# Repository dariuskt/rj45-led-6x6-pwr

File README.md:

---

6x6 ch led dimmer

Dev NOTE: before commit, run `./kibot.sh` to regenerate documentation, bom, gerbers and other assets.

* [schematics.pdf](gen/schematics.pdf)
* [pcb.pdf with dimensions](gen/pcb.pdf)

---

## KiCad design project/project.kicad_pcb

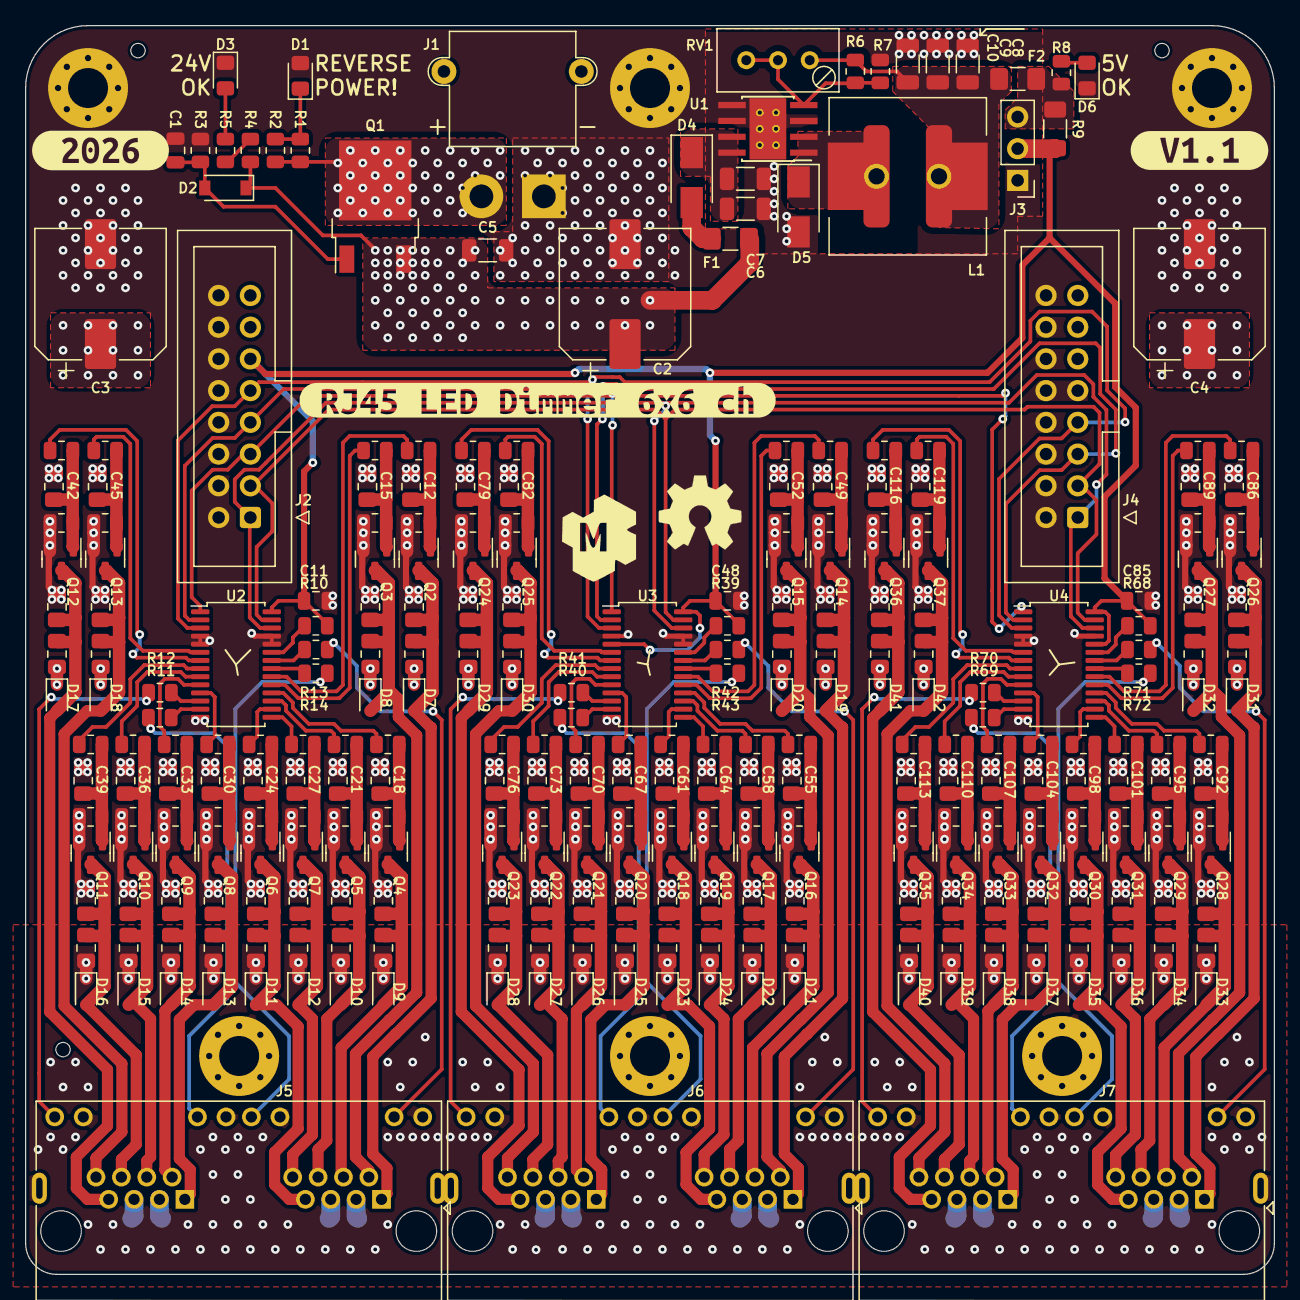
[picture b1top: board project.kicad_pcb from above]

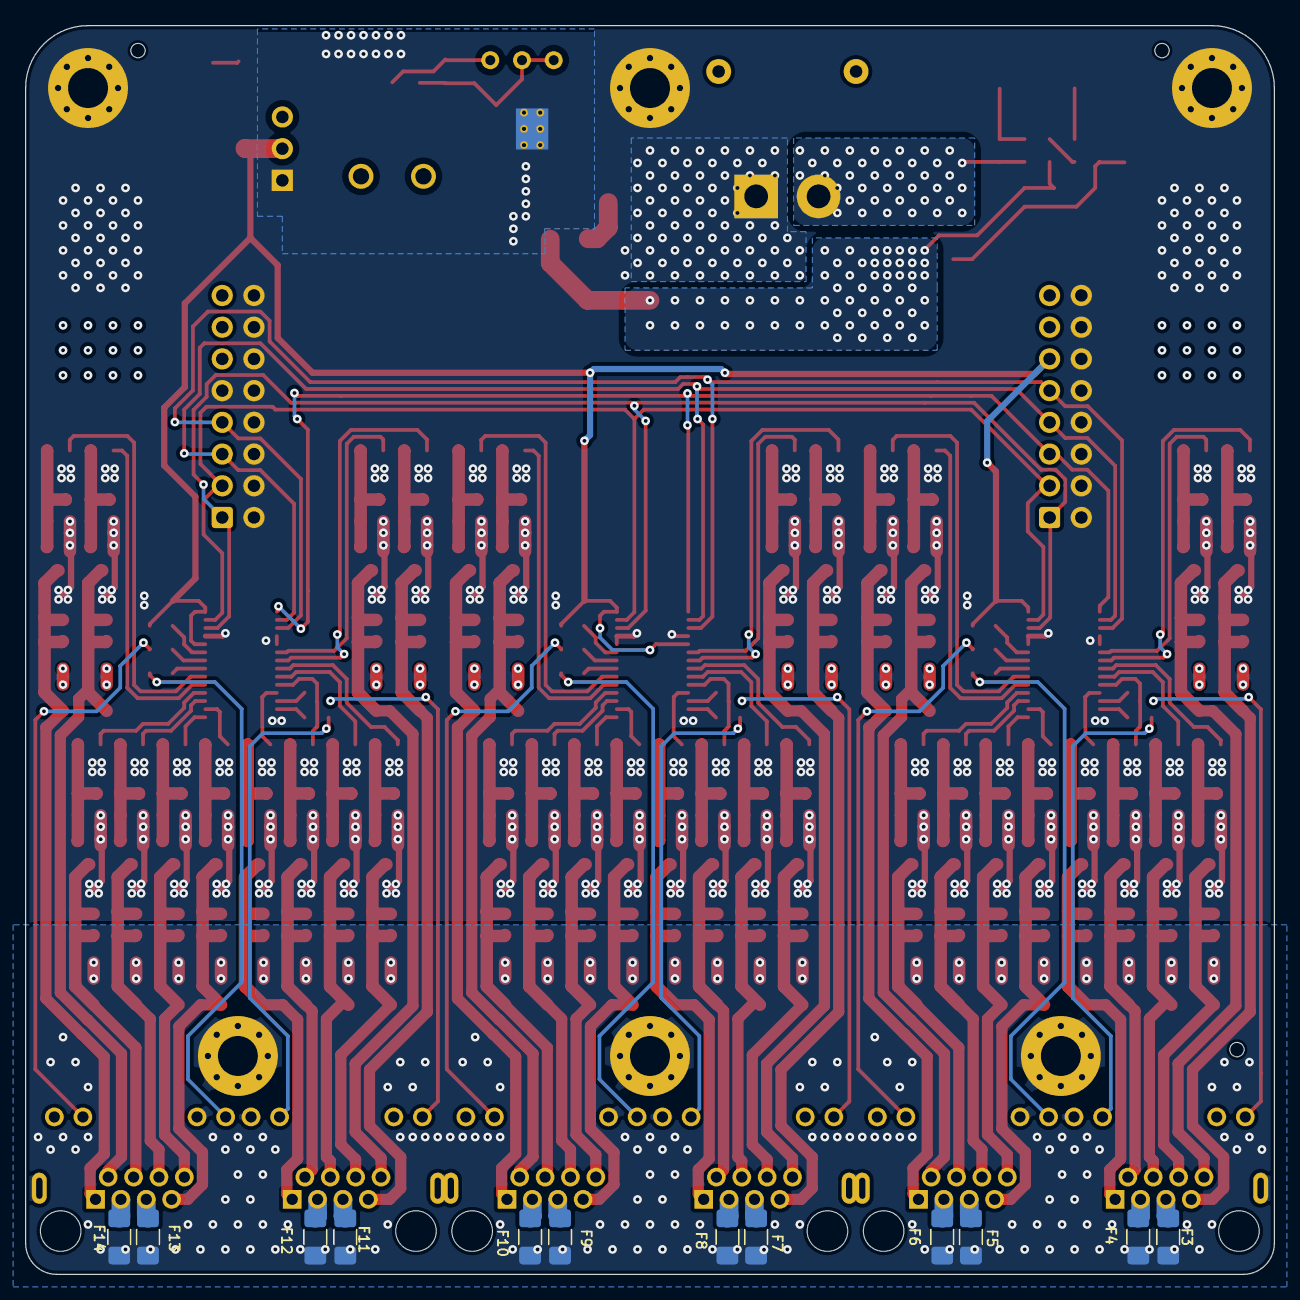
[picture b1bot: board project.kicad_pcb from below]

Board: 4 copper layers, 100.0 x 100.0 mm, 334 parts (12 on the bottom side), 167 nets.

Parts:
C1, C11, C48, C85: 100n; C_0805_2012Metric
C2, C3, C4: 220u/35v; CP_Elec_10x10
C5, C6, C7: 10u/35v; C_1206_3216Metric
C8, C9, C10: 100u/10v; C_1206_3216Metric
C12, C13, C14, C15, C16, C17, C18, C19, C20, C21, C22, C23, C24, C25, C26, C27, C28, C29, C30, C31, C32, C33, C34, C35, C36, C37, C38, C39, C40, C41, C42, C43, C44, C45, C46, C47, C49, C50, C51, C52, C53, C54, C55, C56, C57, C58, C59, C60, C61, C62, C63, C64, C65, C66, C67, C68, C69, C70, C71, C72, C73, C74, C75, C76, C77, C78, C79, C80, C81, C82, C83, C84, C86, C87, C88, C89, C90, C91, C92, C93, C94, C95, C96, C97, C98, C99, C100, C101, C102, C103, C104, C105, C106, C107, C108, C109, C110, C111, C112, C113, C114, C115, C116, C117, C118, C119, C120, C121: 10n; C_0805_2012Metric_Pad1.18x1.45mm_HandSolder
D1: LED-R; LED_0805_2012Metric_Pad1.15x1.40mm_HandSolder
D2: 11V; D_SOD-123
D3, D6: LED-G; LED_0805_2012Metric_Pad1.15x1.40mm_HandSolder
D4, D5: SS34; D_SMA
D7, D8, D9, D10, D11, D12, D13, D14, D15, D16, D17, D18, D19, D20, D21, D22, D23, D24, D25, D26, D27, D28, D29, D30, D31, D32, D33, D34, D35, D36, D37, D38, D39, D40, D41, D42: 1N5819WS; D_SOD-323
F1: 100mA; Fuse_1206_3216Metric_Pad1.42x1.75mm_HandSolder
F2: 300mA; Fuse_1206_3216Metric_Pad1.42x1.75mm_HandSolder
F3, F4, F5, F6, F7, F8, F9, F10, F11, F12, F13, F14: 1A; Fuse_1206_3216Metric_Pad1.42x1.75mm_HandSolder
G1: Logo_Open_Hardware_Large; OSHW-Symbol_6.7x6mm_SilkScreen
G2: LOGO_KMS; logo_kms_small_silkscreen
H1, H2, H3, H4, H5, H6: MP; MountingHole_3.2mm_M3_Pad_Via
J1: XT-IN; AMASS_XT30PW-M_1x02_P2.50mm_Horizontal
J2: IN; IDC-Header_2x08_P2.54mm_Vertical
J3: 5V; PinHeader_1x03_P2.54mm_Vertical
J4: OUT; IDC-Header_2x08_P2.54mm_Vertical
J5, J6, J7: RJ45_LED_Shielded_x2; RJ45_CONNFLY-Elec_DS1129-04-S8B0P-X
L1: 47u/2.5A; L_12x12mm_H8mm__D11.0_P5.0_universal
Q1: HYG210P06LQ1D; TO-252-2
Q2, Q3, Q4, Q5, Q6, Q7, Q8, Q9, Q10, Q11, Q12, Q13, Q14, Q15, Q16, Q17, Q18, Q19, Q20, Q21, Q22, Q23, Q24, Q25, Q26, Q27, Q28, Q29, Q30, Q31, Q32, Q33, Q34, Q35, Q36, Q37: AO3400A; SOT-23
R1, R2, R3, R4, R5, R10, R39, R68: 10k; R_0805_2012Metric
R6, R8, R11, R12, R13, R14, R40, R41, R42, R43, R69, R70, R71, R72: 4k7; R_0805_2012Metric
R7: 1k5; R_0805_2012Metric
R9: 0R1; R_1206_3216Metric_Pad1.30x1.75mm_HandSolder
R15, R17, R19, R21, R23, R25, R27, R29, R31, R33, R35, R37, R44, R46, R48, R50, R52, R54, R56, R58, R60, R62, R64, R66, R73, R75, R77, R79, R81, R83, R85, R87, R89, R91, R93, R95: 1K; R_0805_2012Metric
R16, R18, R20, R22, R24, R26, R28, R30, R32, R34, R36, R38, R45, R47, R49, R51, R53, R55, R57, R59, R61, R63, R65, R67, R74, R76, R78, R80, R82, R84, R86, R88, R90, R92, R94, R96: 100K; R_0805_2012Metric
RV1: 5k; Potentiometer_Bourns_3296W_Vertical
U1: XL4001; Texas_HTSOP-8-1EP_3.9x4.9mm_P1.27mm_EP2.95x4.9mm_Mask2.4x3.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
U2, U3, U4: PCA9685PW; TSSOP-28_4.4x9.7mm_P0.65mm
kibuzzard-69BFE35C: G***; kibuzzard-69BFE35C
kibuzzard-69BFE365: G***; kibuzzard-69BFE365
kibuzzard-67852857: G***; kibuzzard-67852857

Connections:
+5V: C11.1, C48.1, C85.1, J2.11, J3.2, R9.2, R10.1, R39.1, R68.1, U2.28 (VDD), U3.5 (A4), U3.28 (VDD), U4.24 (A5), U4.28 (VDD)
+24V: C2.1, C3.1, C4.1, C5.1, C13.1, C16.1, C19.1, C22.1, C25.1, C28.1, C31.1, C34.1, C37.1, C40.1, C43.1, C46.1, C50.1, C53.1, C56.1, C59.1, C62.1, C65.1, C68.1, C71.1, C74.1, C77.1, C80.1, C83.1, C87.1, C90.1, C93.1, C96.1, C99.1, C102.1, C105.1, C108.1, C111.1, C114.1, C117.1, C120.1, D2.1 (K), D7.1 (K), D8.1 (K), D9.1 (K), D10.1 (K), D11.1 (K), D12.1 (K), D13.1 (K), D14.1 (K), D15.1 (K), D16.1 (K), D17.1 (K), D18.1 (K), D19.1 (K), D20.1 (K), D21.1 (K), D22.1 (K), D23.1 (K), D24.1 (K), D25.1 (K), D26.1 (K), D27.1 (K), D28.1 (K), D29.1 (K), D30.1 (K), D31.1 (K), D32.1 (K), D33.1 (K), D34.1 (K), D35.1 (K), D36.1 (K), D37.1 (K), D38.1 (K), D39.1 (K), D40.1 (K), D41.1 (K), D42.1 (K), F1.1, F3.1, F4.1, F5.1, F6.1, F7.1, F8.1, F9.1, F10.1, F11.1, F12.1, F13.1, F14.1, Q1.3 (S), R4.2
/FB: R6.2, R7.1, RV1.2, RV1.3, U1.4 (FB)
/SW: D5.1 (K), L1.1, U1.1 (SW), U1.2 (SW)
/VIN: J1.2, Q1.2 (D), R1.1, R2.1
/VINp: C6.1, C7.1, D4.1 (K), U1.7 (VIN), U1.8 (VIN)
/VOUTf: F2.2, J3.3, R8.2, R9.1
/VOUTp: C8.1, C9.1, C10.1, F2.1, L1.2, R6.1, RV1.1
/_double_port_pwr1/1Blue: C22.2, C23.1, D10.2 (A), J5.6, Q5.3 (D)
/_double_port_pwr1/1Green: C19.2, C20.1, D9.2 (A), J5.4, Q4.3 (D)
/_double_port_pwr1/1Red: C16.2, C17.1, D8.2 (A), J5.2, Q3.3 (D)
/_double_port_pwr1/1TBD: C25.2, C26.1, D11.2 (A), J5.7, Q6.3 (D)
/_double_port_pwr1/1White2: C28.2, C29.1, D12.2 (A), J5.8, Q7.3 (D)
/_double_port_pwr1/1white1: C13.2, C14.1, D7.2 (A), J5.1, Q2.3 (D)
/_double_port_pwr1/2Blue: C40.2, C41.1, D16.2 (A), J5.18, Q11.3 (D)
/_double_port_pwr1/2Green: C37.2, C38.1, D15.2 (A), J5.16, Q10.3 (D)
/_double_port_pwr1/2Red: C34.2, C35.1, D14.2 (A), J5.14, Q9.3 (D)
/_double_port_pwr1/2TBD: C43.2, C44.1, D17.2 (A), J5.19, Q12.3 (D)
/_double_port_pwr1/2White2: C46.2, C47.1, D18.2 (A), J5.20, Q13.3 (D)
/_double_port_pwr1/2white1: C31.2, C32.1, D13.2 (A), J5.13, Q8.3 (D)
/_double_port_pwr1/LED11: R12.2, U2.12 (LED6)
/_double_port_pwr1/LED12: R11.2, U2.13 (LED7)
/_double_port_pwr1/LED21: R14.2, U2.21 (LED14)
/_double_port_pwr1/LED22: R13.2, U2.22 (LED15)
/_double_port_pwr1/_single_channel_pwr_13/IN: R35.1, U2.7 (LED1)
/_double_port_pwr1/_single_channel_pwr_14/IN: R33.1, U2.8 (LED2)
/_double_port_pwr1/_single_channel_pwr_15/IN: R37.1, U2.6 (LED0)
/_double_port_pwr1/_single_channel_pwr_16/IN: R15.1, U2.20 (LED13)
/_double_port_pwr1/_single_channel_pwr_17/IN: R17.1, U2.19 (LED12)
/_double_port_pwr1/_single_channel_pwr_18/IN: R23.1, U2.16 (LED9)
/_double_port_pwr1/_single_channel_pwr_19/IN: R27.1, U2.11 (LED5)
/_double_port_pwr1/_single_channel_pwr_20/IN: R19.1, U2.18 (LED11)
/_double_port_pwr1/_single_channel_pwr_21/IN: R21.1, U2.17 (LED10)
/_double_port_pwr1/_single_channel_pwr_22/IN: R25.1, U2.15 (LED8)
/_double_port_pwr1/_single_channel_pwr_23/IN: R29.1, U2.10 (LED4)
/_double_port_pwr1/_single_channel_pwr_24/IN: R31.1, U2.9 (LED3)
/_double_port_pwr1//OE: R10.2, U2.23 (~OE)
/_double_port_pwr2/1Blue: C59.2, C60.1, D22.2 (A), J6.6, Q17.3 (D)
/_double_port_pwr2/1Green: C56.2, C57.1, D21.2 (A), J6.4, Q16.3 (D)
/_double_port_pwr2/1Red: C53.2, C54.1, D20.2 (A), J6.2, Q15.3 (D)
/_double_port_pwr2/1TBD: C62.2, C63.1, D23.2 (A), J6.7, Q18.3 (D)
/_double_port_pwr2/1White2: C65.2, C66.1, D24.2 (A), J6.8, Q19.3 (D)
/_double_port_pwr2/1white1: C50.2, C51.1, D19.2 (A), J6.1, Q14.3 (D)
/_double_port_pwr2/2Blue: C77.2, C78.1, D28.2 (A), J6.18, Q23.3 (D)
/_double_port_pwr2/2Green: C74.2, C75.1, D27.2 (A), J6.16, Q22.3 (D)
/_double_port_pwr2/2Red: C71.2, C72.1, D26.2 (A), J6.14, Q21.3 (D)
/_double_port_pwr2/2TBD: C80.2, C81.1, D29.2 (A), J6.19, Q24.3 (D)
/_double_port_pwr2/2White2: C83.2, C84.1, D30.2 (A), J6.20, Q25.3 (D)
/_double_port_pwr2/2white1: C68.2, C69.1, D25.2 (A), J6.13, Q20.3 (D)
/_double_port_pwr2/LED11: R41.2, U3.12 (LED6)
/_double_port_pwr2/LED12: R40.2, U3.13 (LED7)
/_double_port_pwr2/LED21: R43.2, U3.21 (LED14)
/_double_port_pwr2/LED22: R42.2, U3.22 (LED15)
/_double_port_pwr2/_single_channel_pwr_13/IN: R64.1, U3.7 (LED1)
/_double_port_pwr2/_single_channel_pwr_14/IN: R62.1, U3.8 (LED2)
/_double_port_pwr2/_single_channel_pwr_15/IN: R66.1, U3.6 (LED0)
/_double_port_pwr2/_single_channel_pwr_16/IN: R44.1, U3.20 (LED13)
/_double_port_pwr2/_single_channel_pwr_17/IN: R46.1, U3.19 (LED12)
/_double_port_pwr2/_single_channel_pwr_18/IN: R52.1, U3.16 (LED9)
/_double_port_pwr2/_single_channel_pwr_19/IN: R56.1, U3.11 (LED5)
/_double_port_pwr2/_single_channel_pwr_20/IN: R48.1, U3.18 (LED11)
/_double_port_pwr2/_single_channel_pwr_21/IN: R50.1, U3.17 (LED10)
/_double_port_pwr2/_single_channel_pwr_22/IN: R54.1, U3.15 (LED8)
/_double_port_pwr2/_single_channel_pwr_23/IN: R58.1, U3.10 (LED4)
/_double_port_pwr2/_single_channel_pwr_24/IN: R60.1, U3.9 (LED3)
/_double_port_pwr2//OE: R39.2, U3.23 (~OE)
/_double_port_pwr3/1Blue: C96.2, C97.1, D34.2 (A), J7.6, Q29.3 (D)
/_double_port_pwr3/1Green: C93.2, C94.1, D33.2 (A), J7.4, Q28.3 (D)
/_double_port_pwr3/1Red: C90.2, C91.1, D32.2 (A), J7.2, Q27.3 (D)
/_double_port_pwr3/1TBD: C99.2, C100.1, D35.2 (A), J7.7, Q30.3 (D)
/_double_port_pwr3/1White2: C102.2, C103.1, D36.2 (A), J7.8, Q31.3 (D)
/_double_port_pwr3/1white1: C87.2, C88.1, D31.2 (A), J7.1, Q26.3 (D)
/_double_port_pwr3/2Blue: C114.2, C115.1, D40.2 (A), J7.18, Q35.3 (D)
/_double_port_pwr3/2Green: C111.2, C112.1, D39.2 (A), J7.16, Q34.3 (D)
/_double_port_pwr3/2Red: C108.2, C109.1, D38.2 (A), J7.14, Q33.3 (D)
/_double_port_pwr3/2TBD: C117.2, C118.1, D41.2 (A), J7.19, Q36.3 (D)
/_double_port_pwr3/2White2: C120.2, C121.1, D42.2 (A), J7.20, Q37.3 (D)
/_double_port_pwr3/2white1: C105.2, C106.1, D37.2 (A), J7.13, Q32.3 (D)
/_double_port_pwr3/LED11: R70.2, U4.12 (LED6)
/_double_port_pwr3/LED12: R69.2, U4.13 (LED7)
/_double_port_pwr3/LED21: R72.2, U4.21 (LED14)
/_double_port_pwr3/LED22: R71.2, U4.22 (LED15)
/_double_port_pwr3/_single_channel_pwr_13/IN: R93.1, U4.7 (LED1)
/_double_port_pwr3/_single_channel_pwr_14/IN: R91.1, U4.8 (LED2)
/_double_port_pwr3/_single_channel_pwr_15/IN: R95.1, U4.6 (LED0)
/_double_port_pwr3/_single_channel_pwr_16/IN: R73.1, U4.20 (LED13)
/_double_port_pwr3/_single_channel_pwr_17/IN: R75.1, U4.19 (LED12)
/_double_port_pwr3/_single_channel_pwr_18/IN: R81.1, U4.16 (LED9)
/_double_port_pwr3/_single_channel_pwr_19/IN: R85.1, U4.11 (LED5)
/_double_port_pwr3/_single_channel_pwr_20/IN: R77.1, U4.18 (LED11)
/_double_port_pwr3/_single_channel_pwr_21/IN: R79.1, U4.17 (LED10)
/_double_port_pwr3/_single_channel_pwr_22/IN: R83.1, U4.15 (LED8)
/_double_port_pwr3/_single_channel_pwr_23/IN: R87.1, U4.10 (LED4)
/_double_port_pwr3/_single_channel_pwr_24/IN: R89.1, U4.9 (LED3)
/_double_port_pwr3//OE: R68.2, U4.23 (~OE)
A0: J2.5, U2.1 (A0), U3.1 (A0), U4.1 (A0)
A1: J2.7, J4.5, U2.2 (A1), U3.2 (A1), U4.2 (A1)
A2: J2.9, J4.7, U2.3 (A2), U3.3 (A2), U4.3 (A2)
GND: C1.2, C2.2, C3.2, C4.2, C5.2, C6.2, C7.2, C8.2, C9.2, C10.2, C11.2, C12.2, C14.2, C15.2, C17.2, C18.2, C20.2, C21.2, C23.2, C24.2, C26.2, C27.2, C29.2, C30.2, C32.2, C33.2, C35.2, C36.2, C38.2, C39.2, C41.2, C42.2, C44.2, C45.2, C47.2, C48.2, C49.2, C51.2, C52.2, C54.2, C55.2, C57.2, C58.2, C60.2, C61.2, C63.2, C64.2, C66.2, C67.2, C69.2, C70.2, C72.2, C73.2, C75.2, C76.2, C78.2, C79.2, C81.2, C82.2, C84.2, C85.2, C86.2, C88.2, C89.2, C91.2, C92.2, C94.2, C95.2, C97.2, C98.2, C100.2, C101.2, C103.2, C104.2, C106.2, C107.2, C109.2, C110.2, C112.2, C113.2, C115.2, C116.2, C118.2, C119.2, C121.2, D1.2 (A), D3.1 (K), D5.2 (A), D6.1 (K), H1.1, H2.1, H3.1, H4.1, H5.1, H6.1, J1.1, J2.2, J2.4, J2.6, J2.8, J2.10, J2.12, J2.14, J2.16, J3.1, J4.2, J4.4, J4.6, J4.8, J4.9, J4.10, J4.12, J4.14, J4.16, J5.9, J5.11, J5.21, J5.23, J5.SH, J6.9, J6.11, J6.21, J6.23, J6.SH, J7.9, J7.11, J7.21, J7.23, J7.SH, Q2.2 (S), Q3.2 (S), Q4.2 (S), Q5.2 (S), Q6.2 (S), Q7.2 (S), Q8.2 (S), Q9.2 (S), Q10.2 (S), Q11.2 (S), Q12.2 (S), Q13.2 (S), Q14.2 (S), Q15.2 (S), Q16.2 (S), Q17.2 (S), Q18.2 (S), Q19.2 (S), Q20.2 (S), Q21.2 (S), Q22.2 (S), Q23.2 (S), Q24.2 (S), Q25.2 (S), Q26.2 (S), Q27.2 (S), Q28.2 (S), Q29.2 (S), Q30.2 (S), Q31.2 (S), Q32.2 (S), Q33.2 (S), Q34.2 (S), Q35.2 (S), Q36.2 (S), Q37.2 (S), R3.1, R7.2, R16.1, R18.1, R20.1, R22.1, R24.1, R26.1, R28.1, R30.1, R32.1, R34.1, R36.1, R38.1, R45.1, R47.1, R49.1, R51.1, R53.1, R55.1, R57.1, R59.1, R61.1, R63.1, R65.1, R67.1, R74.1, R76.1, R78.1, R80.1, R82.1, R84.1, R86.1, R88.1, R90.1, R92.1, R94.1, R96.1, U1.3 (GND), U1.5 (CS), U1.6 (EN), U1.9 (GND), U2.4 (A3), U2.5 (A4), U2.14 (VSS), U2.24 (A5), U2.25 (EXTCLK), U3.4 (A3), U3.14 (VSS), U3.24 (A5), U3.25 (EXTCLK), U4.4 (A3), U4.5 (A4), U4.14 (VSS), U4.25 (EXTCLK)
unnamed: C1.1, D2.2 (A), Q1.1 (G), R3.2
unnamed: C12.1, Q2.1 (G), R15.2, R16.2
unnamed: C15.1, Q3.1 (G), R17.2, R18.2
unnamed: C18.1, Q4.1 (G), R19.2, R20.2
unnamed: C21.1, Q5.1 (G), R21.2, R22.2
unnamed: C24.1, Q6.1 (G), R23.2, R24.2
unnamed: C27.1, Q7.1 (G), R25.2, R26.2
unnamed: C30.1, Q8.1 (G), R27.2, R28.2
unnamed: C33.1, Q9.1 (G), R29.2, R30.2
unnamed: C36.1, Q10.1 (G), R31.2, R32.2
unnamed: C39.1, Q11.1 (G), R33.2, R34.2
unnamed: C42.1, Q12.1 (G), R35.2, R36.2
unnamed: C45.1, Q13.1 (G), R37.2, R38.2
unnamed: C49.1, Q14.1 (G), R44.2, R45.2
unnamed: C52.1, Q15.1 (G), R46.2, R47.2
unnamed: C55.1, Q16.1 (G), R48.2, R49.2
unnamed: C58.1, Q17.1 (G), R50.2, R51.2
unnamed: C61.1, Q18.1 (G), R52.2, R53.2
unnamed: C64.1, Q19.1 (G), R54.2, R55.2
unnamed: C67.1, Q20.1 (G), R56.2, R57.2
unnamed: C70.1, Q21.1 (G), R58.2, R59.2
unnamed: C73.1, Q22.1 (G), R60.2, R61.2
unnamed: C76.1, Q23.1 (G), R62.2, R63.2
unnamed: C79.1, Q24.1 (G), R64.2, R65.2
unnamed: C82.1, Q25.1 (G), R66.2, R67.2
unnamed: C86.1, Q26.1 (G), R73.2, R74.2
unnamed: C89.1, Q27.1 (G), R75.2, R76.2
unnamed: C92.1, Q28.1 (G), R77.2, R78.2
unnamed: C95.1, Q29.1 (G), R79.2, R80.2
unnamed: C98.1, Q30.1 (G), R81.2, R82.2
unnamed: C101.1, Q31.1 (G), R83.2, R84.2
unnamed: C104.1, Q32.1 (G), R85.2, R86.2
unnamed: C107.1, Q33.1 (G), R87.2, R88.2
unnamed: C110.1, Q34.1 (G), R89.2, R90.2
unnamed: C113.1, Q35.1 (G), R91.2, R92.2
unnamed: C116.1, Q36.1 (G), R93.2, R94.2
unnamed: C119.1, Q37.1 (G), R95.2, R96.2
unnamed: D1.1 (K), R1.2, R2.2
unnamed: D3.2 (A), R5.1
unnamed: D4.2 (A), F1.2
unnamed: D6.2 (A), R8.1
unnamed: F3.2, J5.17
unnamed: F4.2, J5.15
unnamed: F5.2, J5.5
unnamed: F6.2, J5.3
unnamed: F7.2, J6.17
unnamed: F8.2, J6.15
unnamed: F9.2, J6.5
unnamed: F10.2, J6.3
unnamed: F11.2, J7.17
unnamed: F12.2, J7.15
unnamed: F13.2, J7.5
unnamed: F14.2, J7.3
unnamed: J5.10, R13.1
unnamed: J5.12, R14.1
unnamed: J5.22, R11.1
unnamed: J5.24, R12.1
unnamed: J6.10, R42.1
unnamed: J6.12, R43.1
unnamed: J6.22, R40.1
unnamed: J6.24, R41.1
unnamed: J7.10, R71.1
unnamed: J7.12, R72.1
unnamed: J7.22, R69.1
unnamed: J7.24, R70.1
unnamed: R4.1, R5.2
SCL: J2.1, J4.1, U2.26 (SCL), U3.26 (SCL), U4.26 (SCL)
SDA: J2.3, J4.3, U2.27 (SDA), U3.27 (SDA), U4.27 (SDA)

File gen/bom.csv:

"Row","Description","Part","References","Value","Footprint","Quantity Per PCB","Status","Datasheet","LCSC Part Number","lcsc#","jlc-part-type","WE"
"1","Unpolarized capacitor","C","C12,C13,C14,C15,C16,C17,C18,C19,C20,C21,C22,C23,C24,C25,C26,C27,C28,C29,C30,C31,C32,C33,C34,C35,C36,C37,C38,C39,C40,C41,C42,C43,C44,C45,C46,C47,C49,C50,C51,C52,C53,C54,C55,C56,C57,C58,C59,C60,C61,C62,C63,C64,C65,C66,C67,C68,C69,C70,C71,C72,C73,C74,C75,C76,C77,C78,C79,C80,C81,C82,C83,C84,C86,C87,C88,C89,C90,C91,C92,C93,C94,C95,C96,C97,C98,C99,C100,C101,C102,C103,C104,C105,C106,C107,C108,C109,C110,C111,C112,C113,C114,C115,C116,C117,C118,C119,C120,C121","10n","C_0805_2012Metric_Pad1.18x1.45mm_HandSolder","108"," ","~","","C1710","B",""
"2","Unpolarized capacitor","C","C1,C11,C48,C85","100n","C_0805_2012Metric","4"," ","~","","C49678","B",""
"3","Unpolarized capacitor","C","C8,C9,C10","100u/10v","C_1206_3216Metric","3"," ","https://datasheet.lcsc.com/lcsc/1811061115_Murata-Electronic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","","C312983","E",""
"4","Unpolarized capacitor","C","C5,C6,C7","10u/35v","C_1206_3216Metric","3"," ","~","","C13585","B",""
"5","Polarized capacitor","C_Polarized","C2,C3,C4","220u/35v","CP_Elec_10x10","3"," ","~","","C249503","E",""
"6","Zener diode","D_Zener","D2","11V","D_SOD-123","1"," ","","","C22395528","PE",""
"7","Schottky diode","D_Schottky","D7,D8,D9,D10,D11,D12,D13,D14,D15,D16,D17,D18,D19,D20,D21,D22,D23,D24,D25,D26,D27,D28,D29,D30,D31,D32,D33,D34,D35,D36,D37,D38,D39,D40,D41,D42","1N5819WS","D_SOD-323","36"," ","","","C191023","B",""
"8","Light emitting diode, small symbol, filled shape","LED_Small_Filled","D3,D6","LED-G","LED_0805_2012Metric_Pad1.15x1.40mm_HandSolder","2"," ","https://wmsc.lcsc.com/wmsc/upload/file/pdf/v2/lcsc/180615182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","","C2297","B",""
"9","Light emitting diode, small symbol, filled shape","LED_Small_Filled","D1","LED-R","LED_0805_2012Metric_Pad1.15x1.40mm_HandSolder","1"," ","https://jlcpcb.com/api/file/downloadByFileSystemAccessId/855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","","C84256","B",""
"10","40V 3A Schottky Barrier Rectifier Diode, SMA(DO-214AC)","CDBA340-HF","D4,D5","SS34","D_SMA","2"," ","","","C8678","B",""
"11","Fuse","Fuse","F1","100mA","Fuse_1206_3216Metric_Pad1.42x1.75mm_HandSolder","1"," ","https://www.lcsc.com/datasheet/C2830236.pdf?spm=wm.fly.bg.0.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","","C2830236","E",""
"12","Fuse","Fuse","F3,F4,F5,F6,F7,F8,F9,F10,F11,F12,F13,F14","1A","Fuse_1206_3216Metric_Pad1.42x1.75mm_HandSolder","12"," ","https://www.lcsc.com/datasheet/C7542958.pdf","","C7542958","E",""
"13","Fuse","Fuse","F2","300mA","Fuse_1206_3216Metric_Pad1.42x1.75mm_HandSolder","1"," ","https://www.lcsc.com/datasheet/C2897464.pdf","","C2897464","E",""
"14","Generic connector, single row, 01x03, script generated (kicad-library-utils/schlib/autogen/connector/)","Conn_01x03_Male","J3","5V","PinHeader_1x03_P2.54mm_Vertical","1"," ","~","","","-",""
"15","Generic connector, double row, 02x08, odd/even pin numbering scheme (row 1 odd numbers, row 2 even numbers), script generated (kicad-library-utils/schlib/autogen/connector/)","Conn_02x08_Odd_Even","J2,J4","IN","IDC-Header_2x08_P2.54mm_Vertical","2"," ","~","","C3406","E",""
"16","RJ connector, 8P8C (8 positions 8 connected), two LEDs, Shielded, two ports","RJ45_LED_Shielded_x2","J5,J6,J7","RJ45_LED_Shielded_x2","RJ45_CONNFLY-Elec_DS1129-04-S8B0P-X","3"," ","https://www.lcsc.com/datasheet/lcsc_datasheet_1811141116_CON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","","C86581","E",""
"17","Generic connector, double row, 02x01, this symbol is compatible with counter-clockwise, top-bottom and odd-even numbering schemes., script generated (kicad-library-utils/schlib/autogen/connector/)","Conn_02x01","J1","XT-IN","AMASS_XT30PW-M_1x02_P2.50mm_Horizontal","1"," ","https://www.lcsc.com/datasheet/lcsc_datasheet_2304140030_Cha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","","C431092","E",""
"18","Inductor","L","L1","47u/2.5A","L_12x12mm_H8mm__D11.0_P5.0_universal","1"," ","https://datasheet.lcsc.com/lcsc/2201121400_SHOU-HAN-CYH127-4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","","C2929503","E",""
"19","30V Vds, 5.7A Id, N-Channel MOSFET, SOT-23","AO3400A","Q2,Q3,Q4,Q5,Q6,Q7,Q8,Q9,Q10,Q11,Q12,Q13,Q14,Q15,Q16,Q17,Q18,Q19,Q20,Q21,Q22,Q23,Q24,Q25,Q26,Q27,Q28,Q29,Q30,Q31,Q32,Q33,Q34,Q35,Q36,Q37","AO3400A","SOT-23","36"," ","http://www.aosmd.com/pdfs/datasheet/AO3400A.pdf","","C20917","B",""
"20","P-MOSFET transistor, gate/drain/source","Q_PMOS_GDS","Q1","HYG210P06LQ1D","TO-252-2","1"," ","~","","C2834760","E",""
"21","Resistor","R","R9","0R1","R_1206_3216Metric_Pad1.30x1.75mm_HandSolder","1"," ","~","","C25334","B",""
"22","Resistor","R","R15,R17,R19,R21,R23,R25,R27,R29,R31,R33,R35,R37,R44,R46,R48,R50,R52,R54,R56,R58,R60,R62,R64,R66,R73,R75,R77,R79,R81,R83,R85,R87,R89,R91,R93,R95","1K","R_0805_2012Metric","36"," ","~","","C17513","B",""
"23","Resistor","R","R7","1k5","R_0805_2012Metric","1"," ","~","","C4310","B",""
"24","Resistor","R","R6,R8,R11,R12,R13,R14,R40,R41,R42,R43,R69,R70,R71,R72","4k7","R_0805_2012Metric","14"," ","~","","C17673","B",""
"25","Resistor","R","R1,R2,R3,R4,R5,R10,R39,R68","10k","R_0805_2012Metric","8"," ","~","","C17414","B",""
"26","Resistor","R","R16,R18,R20,R22,R24,R26,R28,R30,R32,R34,R36,R38,R45,R47,R49,R51,R53,R55,R57,R59,R61,R63,R65,R67,R74,R76,R78,R80,R82,R84,R86,R88,R90,R92,R94,R96","100K","R_0805_2012Metric","36"," ","~","","C149504","B",""
"27","Trim-potentiometer","R_Potentiometer_Trim","RV1","5k","Potentiometer_Bourns_3296W_Vertical","1"," ","https://datasheet.lcsc.com/lcsc/1811071811_BOCHEN-Chengdu-Gu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","","C118954","E",""
"28","16-channel 12-bit PWM Fm+ I2C-bus LED controller RGBA TSSOP","PCA9685PW","U2,U3,U4","PCA9685PW","TSSOP-28_4.4x9.7mm_P0.65mm","3"," ","https://www.lcsc.com/datasheet/lcsc_datasheet_2405281434_NXP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","","C2678753","E",""
"29","","XL4001","U1","XL4001","Texas_HTSOP-8-1EP_3.9x4.9mm_P1.27mm_EP2.95x4.9mm_Mask2.4x3.1mm_ThermalVias","1"," ","https://datasheet.lcsc.com/szlcsc/XL4001E1_C73347.pdf","","C2988027","E",""

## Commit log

2025-01-13 2ch grouping layout
2025-01-13 more layout
2025-01-13 prepared for production
2025-01-14 removing dates from gerbers
2026-03-22 improvements after first prototype test
